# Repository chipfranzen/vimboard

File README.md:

# Vimboard
A custom keyboard, ergonomically designed for optimal vim-motion navigation. The very pinnacle of practicality.

## Keymap
Keys are `H`, `J`, `K`, `L`, with a layer key at the thumb. Layer 2 is `W`, `E`, `B`, `T`.

## Hardware
Kailh sunset choc v1 switches with hotswap sockets. Adafruit KB2024 microcontroller, also socketed.

## Licensing
- All original Vimboard files (PCB, schematics, and keymaps) are licensed under the MIT License (see LICENSE).
- QMK Firmware is licensed under GPLv2. See [QMK’s license](https://github.com/qmk/qmk_firmware/blob/master/LICENSE).
- Ergogen is licensed under MIT.
- KiCad files are original works and licensed under MIT.

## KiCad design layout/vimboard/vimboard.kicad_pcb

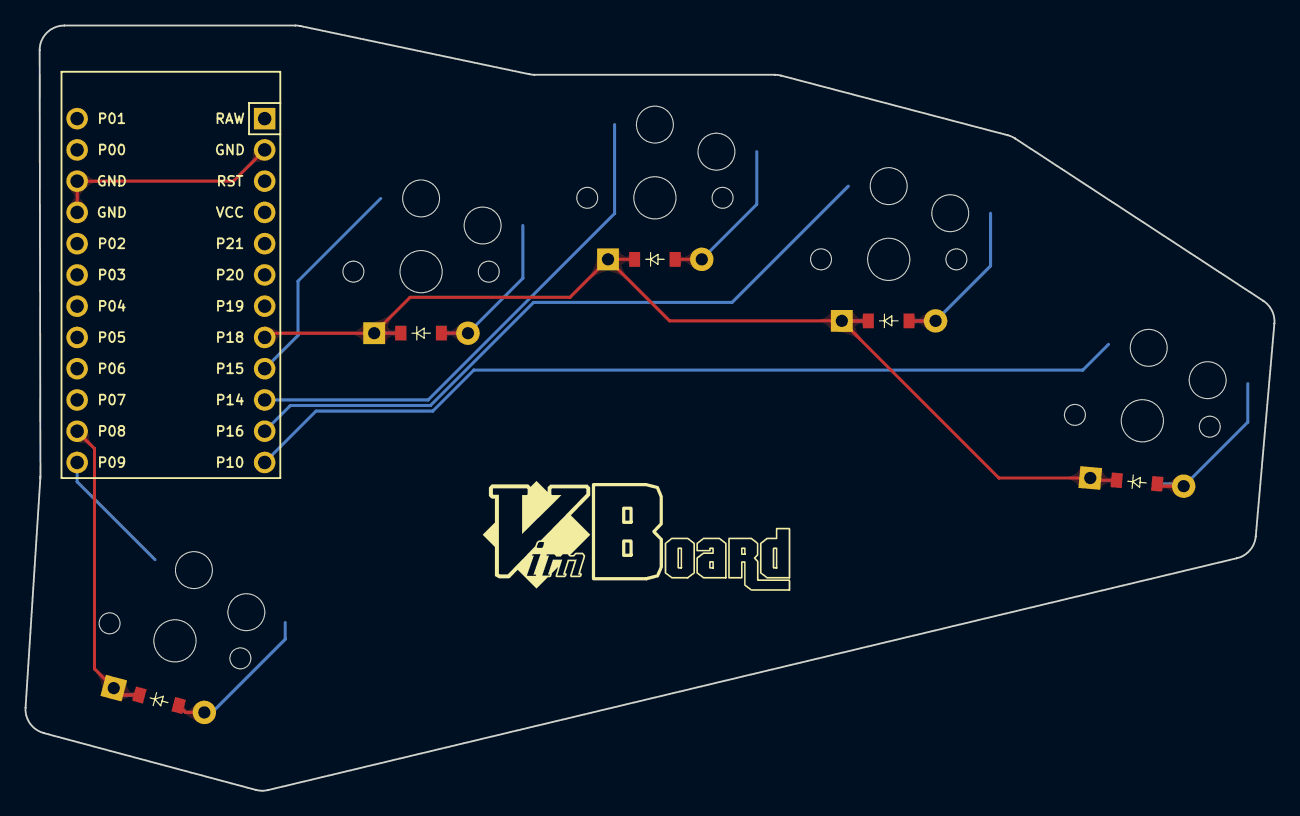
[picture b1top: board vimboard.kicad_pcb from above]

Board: 2 copper layers, 101.5 x 62.2 mm, 12 parts (0 on the bottom side), 13 nets.

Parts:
D1, D2, D3, D4, D5: ComboDiode
MCU1: ProMicro
S1, S2, S3, S4, S5: PG1350
svg2mod: G***; logo

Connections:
GND: MCU1.2, MCU1.15, MCU1.16
P8: D5.1, MCU1.23
P9: MCU1.24, S5.1
P10: MCU1.12, S4.1
P14: MCU1.10, S2.1
P15: MCU1.9, S1.1
P16: MCU1.11, S3.1
P18: D1.1, D2.1, D3.1, D4.1, MCU1.8
escape_main: D5.2, S5.2
index_main: D1.2, S1.2
middle_main: D2.2, S2.2
pinky_main: D4.2, S4.2
ring_main: D3.2, S3.2

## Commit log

2025-06-19 Add layout files.
2025-06-19 Add README.
2025-06-25 Create pcb.
2025-06-25 Update gitignore and remove unneeded files.
2025-07-27 Update budget and notes.
2025-07-27 Complete v1.
